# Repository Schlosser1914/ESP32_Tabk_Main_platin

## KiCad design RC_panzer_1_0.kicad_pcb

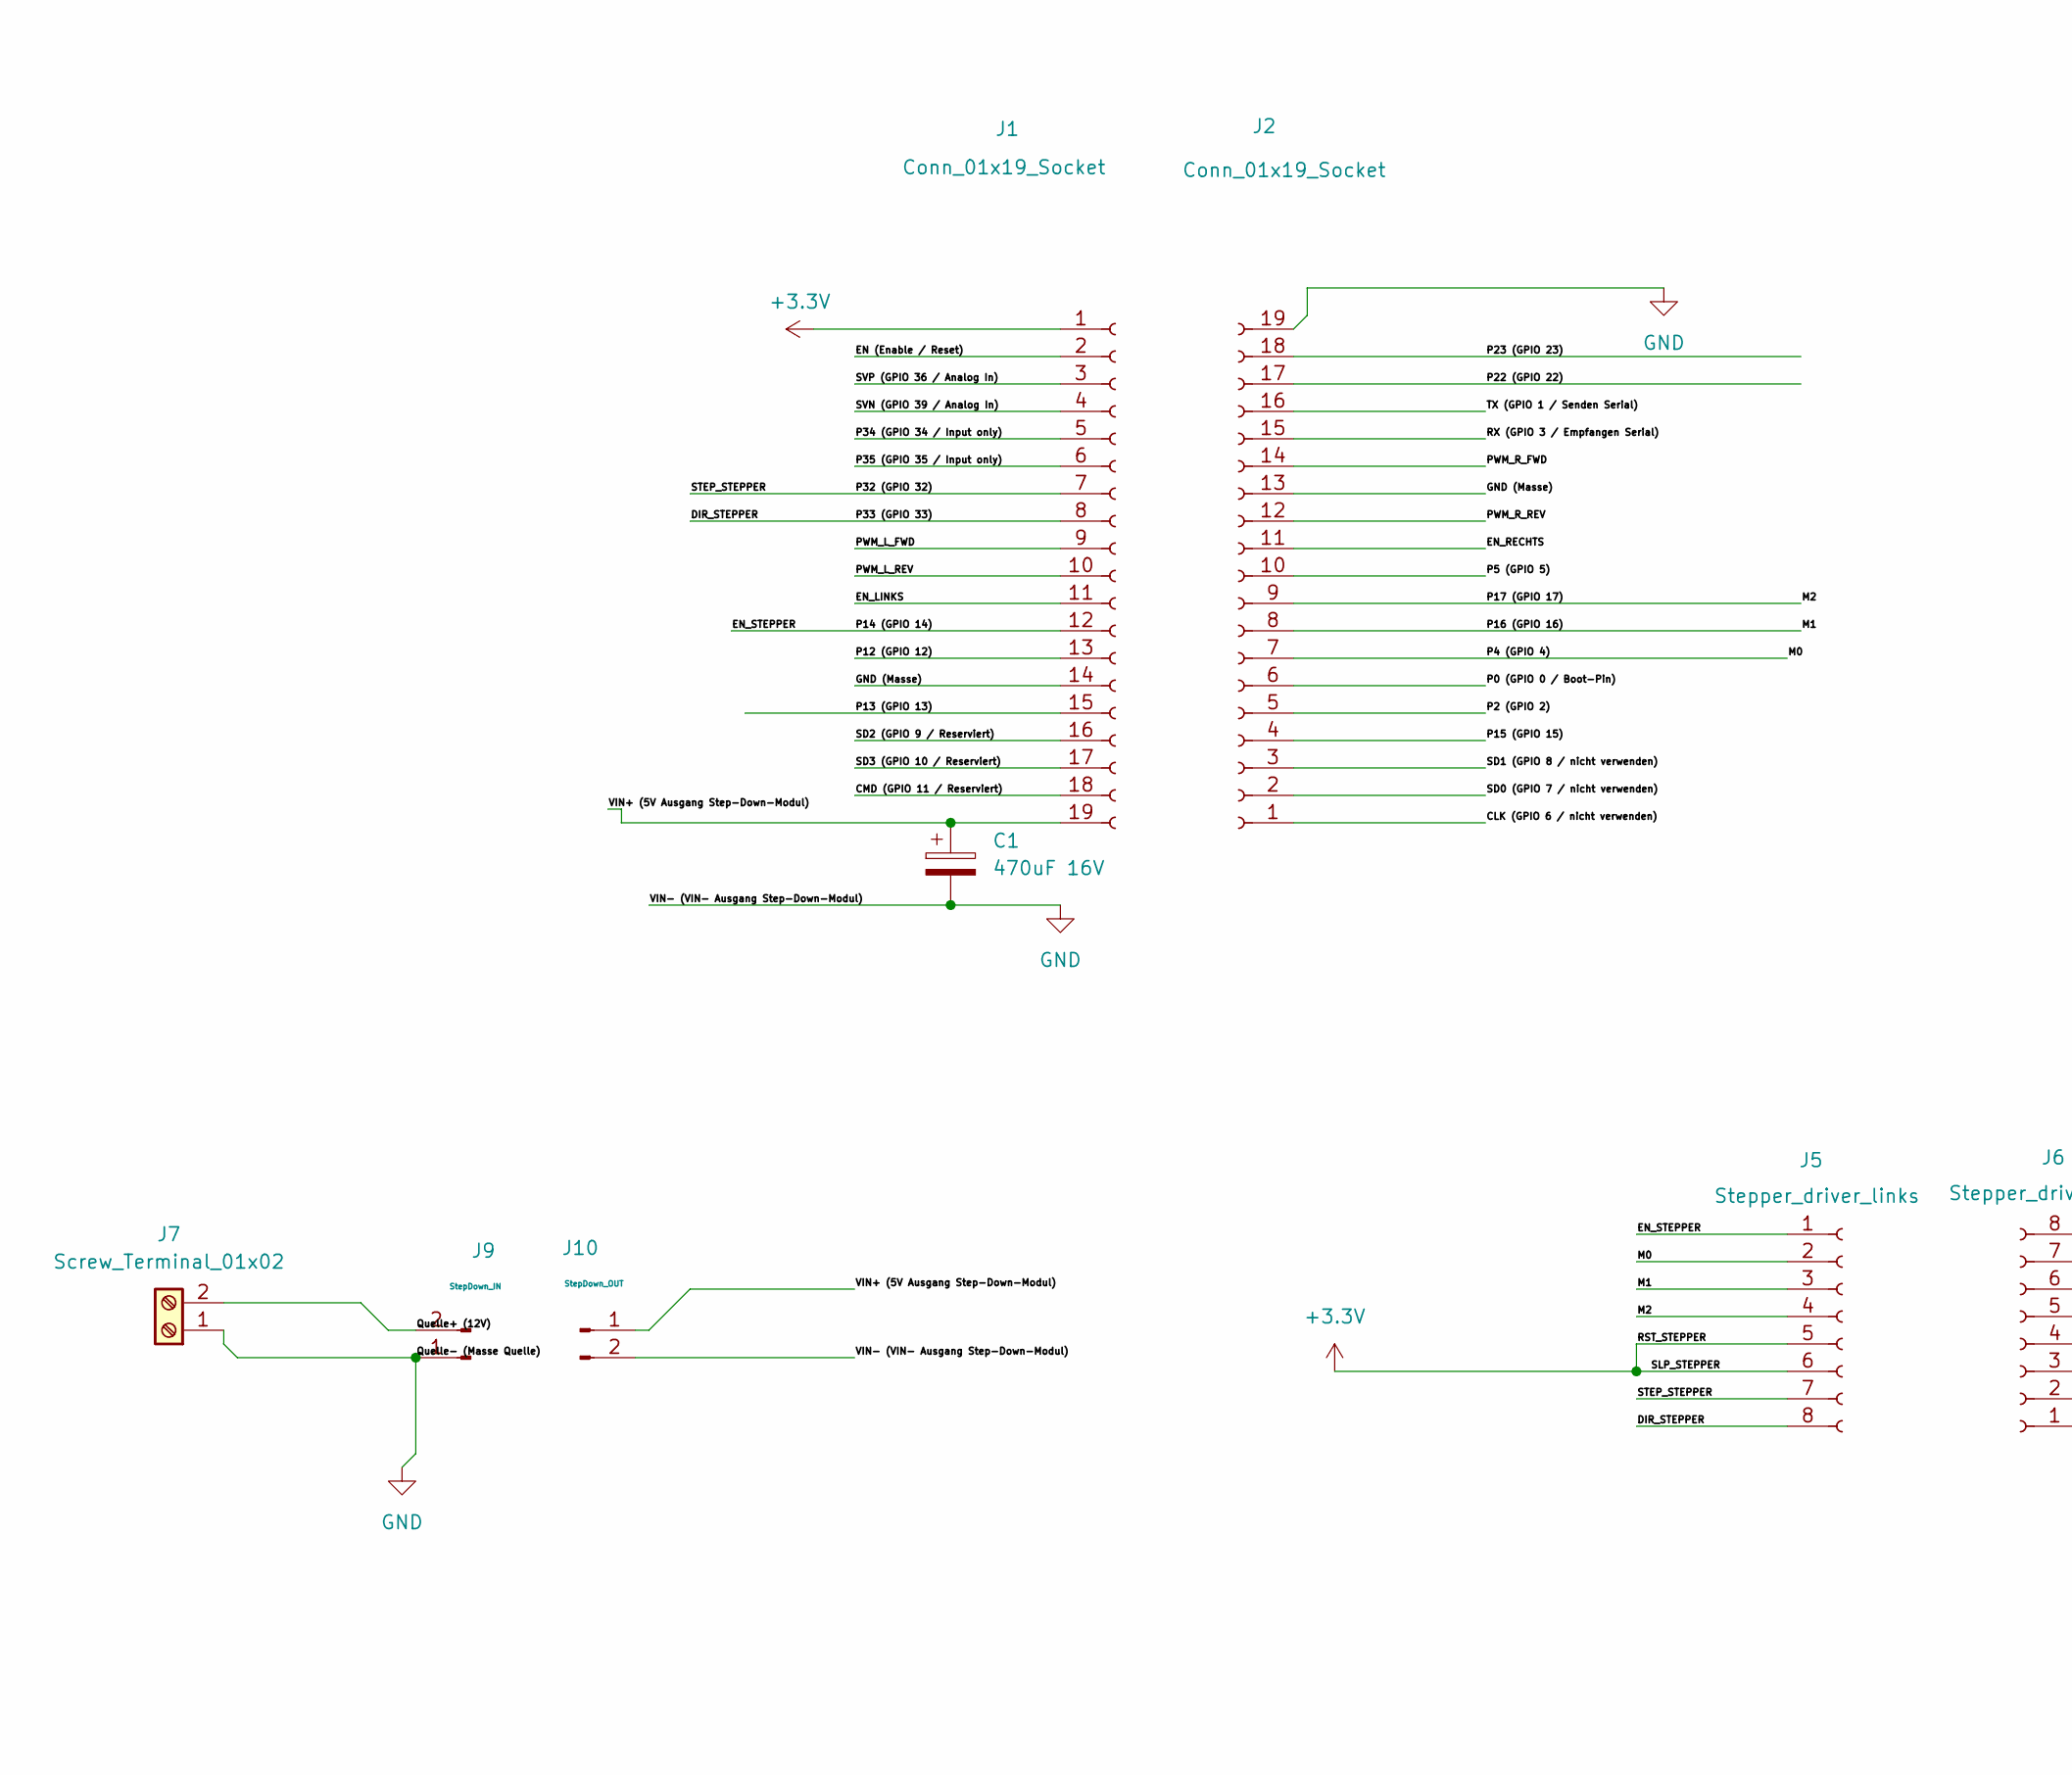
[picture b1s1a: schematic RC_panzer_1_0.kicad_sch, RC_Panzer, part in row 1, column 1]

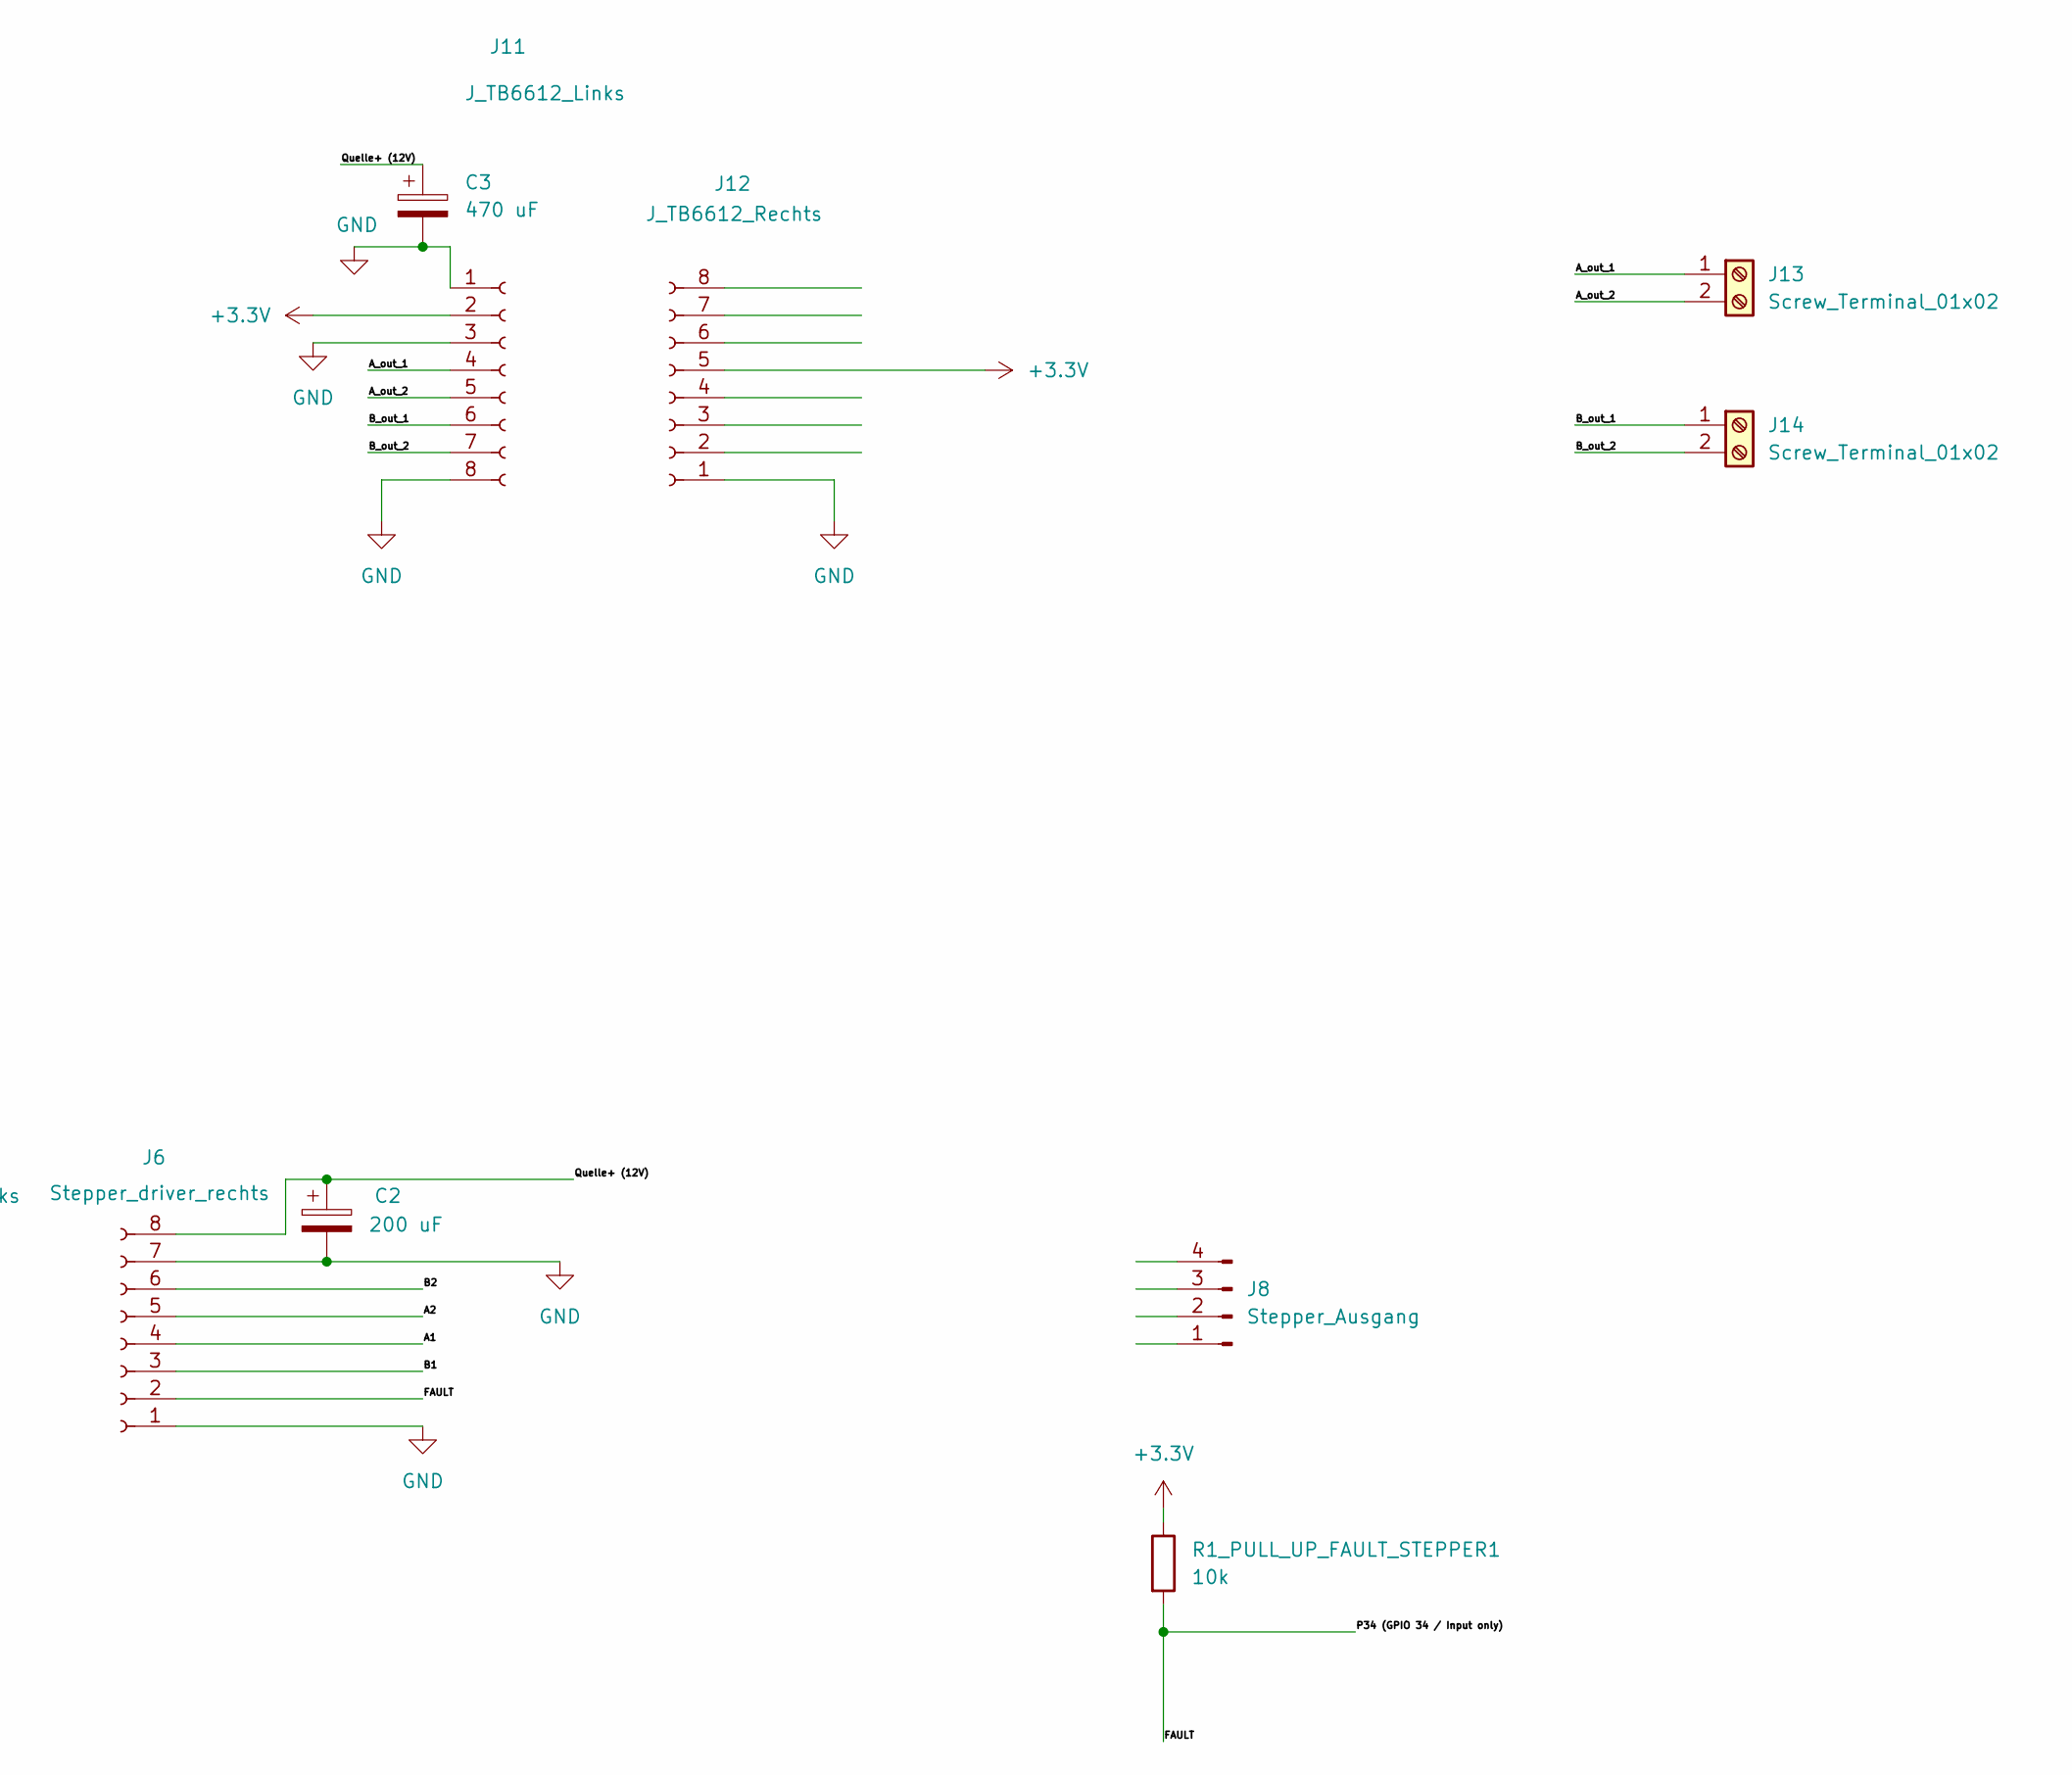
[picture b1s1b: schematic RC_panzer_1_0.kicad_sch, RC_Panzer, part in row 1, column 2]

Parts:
C1: 470uF 16V; CP_Radial_D10.0mm_P3.50mm
C2: 200 uF; CP_Radial_D8.0mm_P5.00mm
C3: 470 uF; CP_Radial_D10.0mm_P5.00mm
J1, J2: Conn_01x19_Socket; PinSocket_1x19_P2.54mm_Vertical
J5: Stepper_driver_links; PinSocket_1x08_P2.54mm_Vertical
J6: Stepper_driver_rechts; PinSocket_1x08_P2.54mm_Vertical
J7, J13, J14: Screw_Terminal_01x02; TerminalBlock_Phoenix_MKDS-1,5-2_1x02_P5.00mm_Horizontal
J8: Stepper_Ausgang; JST_XH_B4B-XH-A_1x04_P2.50mm_Vertical
J9: StepDown_IN; PinHeader_1x02_P2.54mm_Vertical
J10: StepDown_OUT; PinHeader_1x02_P2.54mm_Vertical
J11: J_TB6612_Links; PinSocket_1x08_P2.54mm_Vertical
J12: J_TB6612_Rechts; PinSocket_1x08_P2.54mm_Vertical
R1_PULL_UP_FAULT_STEPPER1: 10k; R_Axial_DIN0207_L6.3mm_D2.5mm_P10.16mm_Horizontal

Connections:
+3.3V: J1.1, J5.5, J5.6, J11.2, J12.5, R1_PULL_UP_FAULT_STEPPER1.1
/<NO NET>: J1.14, J2.13
/A1: J6.4
/A2: J6.5
/A_out_1: J11.4, J13.1
/A_out_2: J11.5, J13.2
/B1: J6.3
/B2: J6.6
/B_out_1: J11.6, J14.1
/B_out_2: J11.7, J14.2
/CLK (GPIO 6 / nicht verwenden): J2.1
/CMD (GPIO 11 / Reserviert): J1.18
/DIR_STEPPER: J1.8, J5.8
/EN (Enable / Reset): J1.2
/EN_LINKS: J1.11
/EN_RECHTS: J2.11
/EN_STEPPER: J1.12, J5.1
/FAULT: J1.5, J6.2, R1_PULL_UP_FAULT_STEPPER1.2
/M0: J2.7, J5.2
/M1: J2.8, J5.3
/M2: J2.9, J5.4
/P0 (GPIO 0 / Boot-Pin): J2.6
/P2 (GPIO 2): J2.5
/P5 (GPIO 5): J2.10
/P12 (GPIO 12): J1.13
/P13 (GPIO 13): J1.15
/P15 (GPIO 15): J2.4
/P22 (GPIO 22): J2.17
/P23 (GPIO 23): J2.18
/P32 (GPIO 32): J1.7, J5.7
/P35 (GPIO 35 / Input only): J1.6
/PWM_L_FWD: J1.9
/PWM_L_REV: J1.10
/PWM_R_FWD: J2.14
/PWM_R_REV: J2.12
/Quelle+ (12V): C2.1, C3.1, J6.8, J7.2, J9.2
/RX (GPIO 3 / Empfangen Serial): J2.15
/SD0 (GPIO 7 / nicht verwenden): J2.2
/SD1 (GPIO 8 / nicht verwenden): J2.3
/SD2 (GPIO 9 / Reserviert): J1.16
/SD3 (GPIO 10 / Reserviert): J1.17
/SVN (GPIO 39 / Analog In): J1.4
/SVP (GPIO 36 / Analog In): J1.3
/TX (GPIO 1 / Senden Serial): J2.16
/VIN+ (5V Ausgang Step-Down-Modul): C1.1, J1.19, J10.1
GND: C1.2, C2.2, C3.2, J2.19, J6.1, J6.7, J7.1, J9.1, J10.2, J11.1, J11.3, J11.8, J12.1

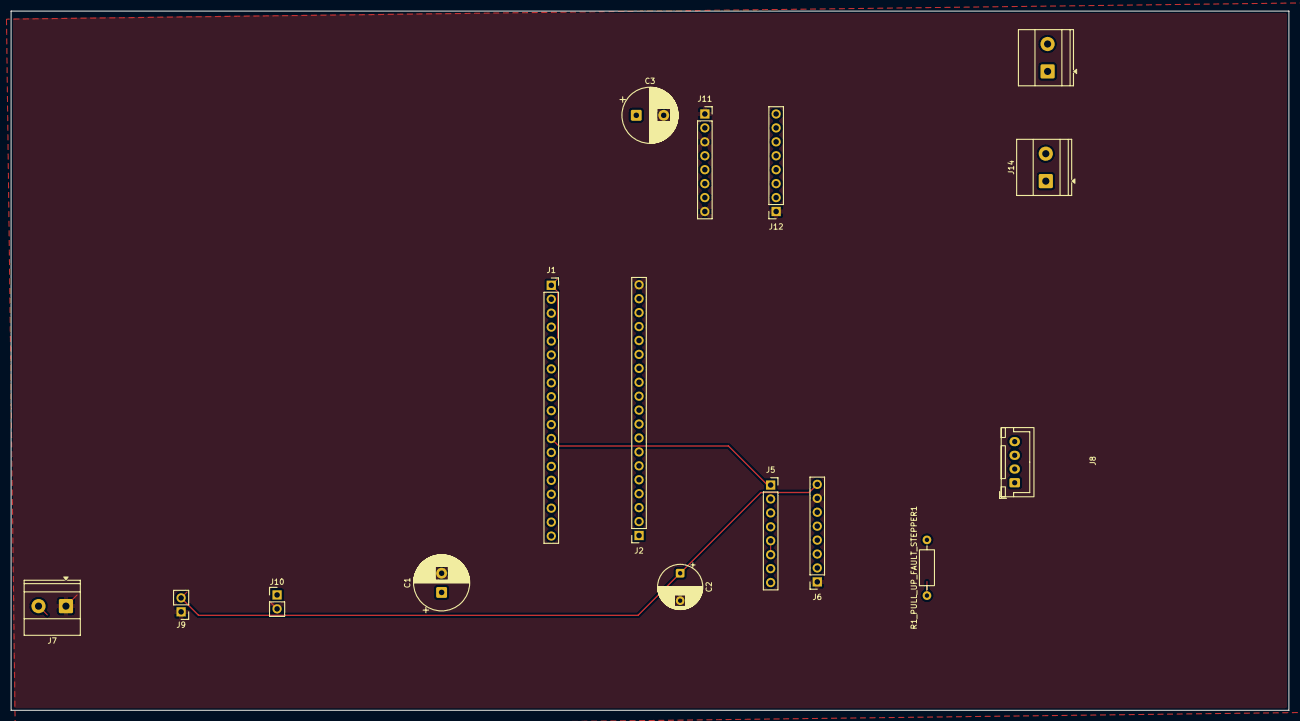
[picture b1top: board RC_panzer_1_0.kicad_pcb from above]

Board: 2 copper layers, 233.0 x 127.5 mm, 16 parts (0 on the bottom side), 16 nets.
